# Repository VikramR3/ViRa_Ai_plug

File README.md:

# ViRa AI Plug

A 2-layer ESP32-S3 mains smart plug: an HLK-5M05 isolated module drops 230 V AC to 5 V, an AMS1117 supplies the ESP32-S3-WROOM-1, and an SRD-05VDC relay switches the outlet through a low-side AO3400A MOSFET with a flyback diode and status LED. A DS3231M with a CR1220 backup cell keeps time for scheduled switching, with six buttons and a buzzer for local control and USB-C for programming. Designed in KiCad 10.

## Warning — mains voltage

This board carries 230 V AC. The mains and low-voltage sections are separated by a documented barrier — 6.78 mm of creepage in the open board area, enforced by `ViRa_V1.0.kicad_dru`. However the tightest mains-to-low-voltage gap is **2.10 mm**, at the relay's mains common pad, which is below the 2.5 mm functional minimum and needs the relay or the power module re-placed to fix. It has not been fabricated or tested. Do not connect it to mains.

Circuit topology follows the open-source Zeen-AI-Plug smart plug.

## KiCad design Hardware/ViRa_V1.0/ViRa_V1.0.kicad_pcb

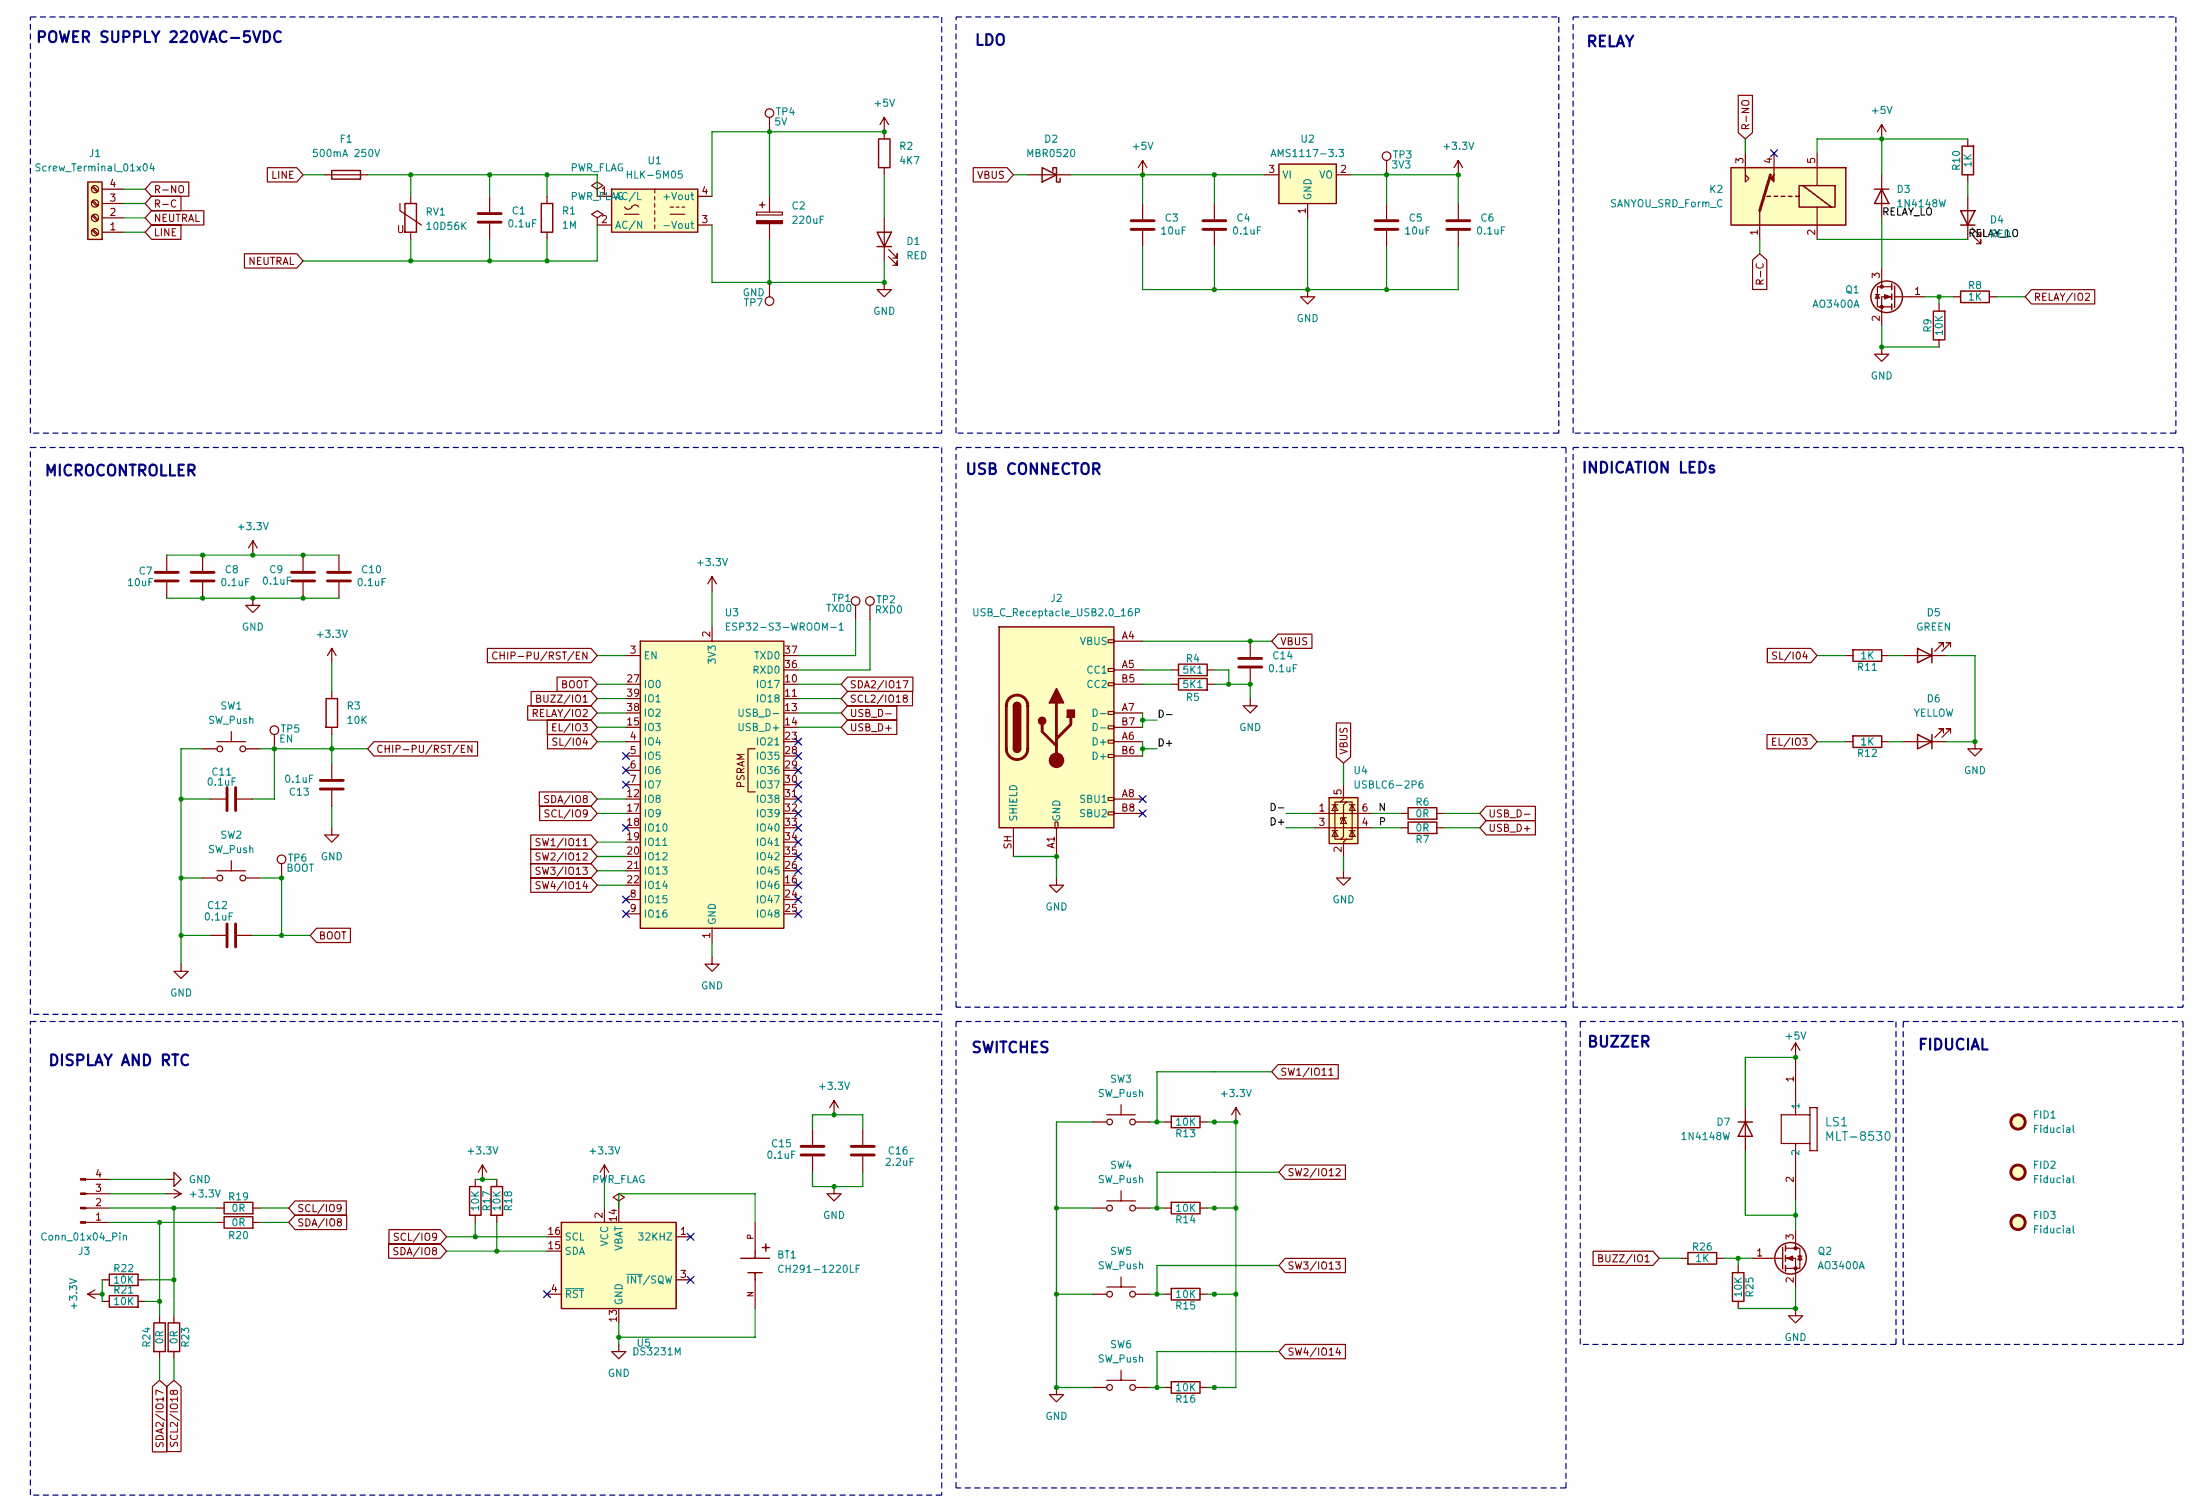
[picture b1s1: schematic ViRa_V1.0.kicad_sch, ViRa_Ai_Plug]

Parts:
BT1: CH291-1220LF; BAT_CH291-1220LF; PARTREV A
C1: 0.1uF; C_Rect_L13.0mm_W6.0mm_P10.00mm_FKS3_FKP3_MKS4
C2: 220uF; CP_Elec_8x10
C3, C5, C7: 10uF; C_0805_2012Metric
C4, C6, C8, C9, C10, C11, C12, C13, C14, C15: 0.1uF; C_0603_1608Metric
C16: 2.2uF; C_0805_2012Metric
D1: RED; LED_D3.0mm
D2: MBR0520; D_SOD-123
D3, D7: 1N4148W; D_SOD-123
D4: RED; LED_0603_1608Metric
D5: GREEN; LED_D3.0mm
D6: YELLOW; LED_D3.0mm
F1: 500mA 250V; Fuse_Littelfuse_395Series
FID1, FID2, FID3: Fiducial; Fiducial_0.75mm_Mask1.5mm
J1: Screw_Terminal_01x04; TerminalBlock_MaiXu_MX126-5.0-04P_1x04_P5.00mm
J2: USB_C_Receptacle_USB2.0_16P; USB_C_Receptacle_HCTL_HC-TYPE-C-16P-01A
J3: Conn_01x04_Pin; PinHeader_1x04_P2.54mm_Vertical
K2: SANYOU_SRD_Form_C; Relay_SPDT_SANYOU_SRD_Series_Form_C
LS1: MLT-8530; MLT-8530_JHE
Q1, Q2: AO3400A; SOT-23
R1: 1M; R_Axial_DIN0207_L6.3mm_D2.5mm_P7.62mm_Horizontal
R2: 4K7; R_0603_1608Metric
R3, R9, R13, R14, R15, R16, R17, R18, R21, R22, R25: 10K; R_0603_1608Metric
R4, R5: 5K1; R_0603_1608Metric
R6, R7, R19, R20, R23, R24: 0R; R_0603_1608Metric
R8, R10, R11, R12, R26: 1K; R_0603_1608Metric
RV1: 10D56K; RV_Disc_D12mm_W5mm_P7.5mm
SW1, SW2, SW3, SW4, SW5, SW6: SW_Push; SW_PUSH_6mm
TP1: TXD0; TestPoint_Pad_D1.5mm
TP2: RXD0; TestPoint_Pad_D1.5mm
TP3: 3V3; TestPoint_Pad_D1.5mm
TP4: 5V; TestPoint_Pad_D1.5mm
TP5: EN; TestPoint_Pad_D1.5mm
TP6: BOOT; TestPoint_Pad_D1.5mm
TP7: GND; TestPoint_Pad_D1.5mm
U1: HLK-5M05; Converter_ACDC_Hi-Link_HLK-5Mxx
U2: AMS1117-3.3; SOT-223-3_TabPin2
U3: ESP32-S3-WROOM-1
U4: USBLC6-2P6; SOT-666
U5: DS3231M; SOIC-16W_7.5x10.3mm_P1.27mm

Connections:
+3.3V: C5.1, C6.1, C7.1, C8.1, C9.1, C10.1, C15.2, C16.1, J3.3, R3.1, R13.1, R14.1, R15.1, R16.1, R17.1, R18.1, R21.1, R22.1, TP3.1 (1_1), U2.2 (VO), U3.2 (3V3), U5.2 (VCC)
+5V: C2.1, C3.1, C4.1, D2.1 (K), D3.1 (K), D7.1 (K), K2.5, LS1.1, R2.1, R10.2, TP4.1 (1_1), U1.4 (+Vout), U2.3 (VI)
/D+: J2.A6 (D+), J2.B6 (D+), U4.3 (I/O2)
/D-: J2.A7 (D-), J2.B7 (D-), U4.1 (I/O1)
/N: R6.1, U4.6 (I/O1)
/P: R7.1, U4.4 (I/O2)
/RELAY_LO: D3.2 (A), D4.1 (K), K2.2, Q1.3 (D)
BOOT: C12.2, SW2.2, TP6.1 (1_1), U3.27 (IO0)
BUZZ/IO1: R26.2, U3.39 (IO1)
CHIP-PU/RST/EN: C11.2, C13.2, R3.2, SW1.2, TP5.1 (1_1), U3.3 (EN)
EL/IO3: R12.2, U3.15 (IO3)
GND: BT1.N, C2.2, C3.2, C4.2, C5.2, C6.2, C7.2, C8.2, C9.2, C10.2, C11.1, C12.1, C13.1, C14.2, C15.1, C16.2, D1.1 (K), D5.1 (K), D6.1 (K), J2.A1 (GND), J2.A12 (GND), J2.B1 (GND), J2.B12 (GND), J2.SH (SHIELD), J3.4, Q1.2 (S), Q2.2 (S), R4.2, R5.2, R9.1, R25.1, SW1.1, SW2.1, SW3.1, SW4.1, SW5.1, SW6.1, TP7.1 (1_1), U1.3 (-Vout), U2.1 (GND), U3.1 (GND), U3.40 (GND), U3.41 (GND), U4.2 (GND), U5.5 (GND), U5.6 (GND), U5.7 (GND), U5.8 (GND), U5.9 (GND), U5.10 (GND), U5.11 (GND), U5.12 (GND), U5.13 (GND)
LINE: F1.1, J1.1
unnamed: D1.2 (A), R2.2
unnamed: D4.2 (A), R10.1
unnamed: D5.2 (A), R11.1
unnamed: D6.2 (A), R12.1
unnamed: D7.2 (A), LS1.2, Q2.3 (D)
unnamed: J2.A5 (CC1), R4.1
unnamed: J2.B5 (CC2), R5.1
unnamed: J3.1, R20.1, R21.2, R24.1
unnamed: J3.2, R19.1, R22.2, R23.1
unnamed: Q1.1 (G), R8.1, R9.2
unnamed: Q2.1 (G), R25.2, R26.1
unnamed: TP2.1 (1_1), U3.36 (RXD0)
unnamed: TP1.1 (1_1), U3.37 (TXD0)
R-C: J1.3, K2.1
R-NO: J1.4, K2.3
RELAY/IO2: R8.2, U3.38 (IO2)
SCL2/IO18: R23.2, U3.11 (IO18)
SCL/IO9: R17.2, R19.2, U3.17 (IO9), U5.16 (SCL)
SDA2/IO17: R24.2, U3.10 (IO17)
SDA/IO8: R18.2, R20.2, U3.12 (IO8), U5.15 (SDA)
SL/I04: R11.2, U3.4 (IO4)
SW1/IO11: R13.2, SW3.2, U3.19 (IO11)
SW2/IO12: R14.2, SW4.2, U3.20 (IO12)
SW3/IO13: R15.2, SW5.2, U3.21 (IO13)
SW4/IO14: R16.2, SW6.2, U3.22 (IO14)
USB_D+: R7.2, U3.14 (USB_D+)
USB_D-: R6.2, U3.13 (USB_D-)
VBUS: C14.1, D2.2 (A), J2.A4 (VBUS), J2.A9 (VBUS), J2.B4 (VBUS), J2.B9 (VBUS), U4.5 (VBUS)

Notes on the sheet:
FIDUCIAL
DISPLAY AND RTC
USB CONNECTOR
LDO
POWER SUPPLY 220VAC-5VDC
INDICATION LEDs
MICROCONTROLLER
BUZZER
RELAY
SWITCHES

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
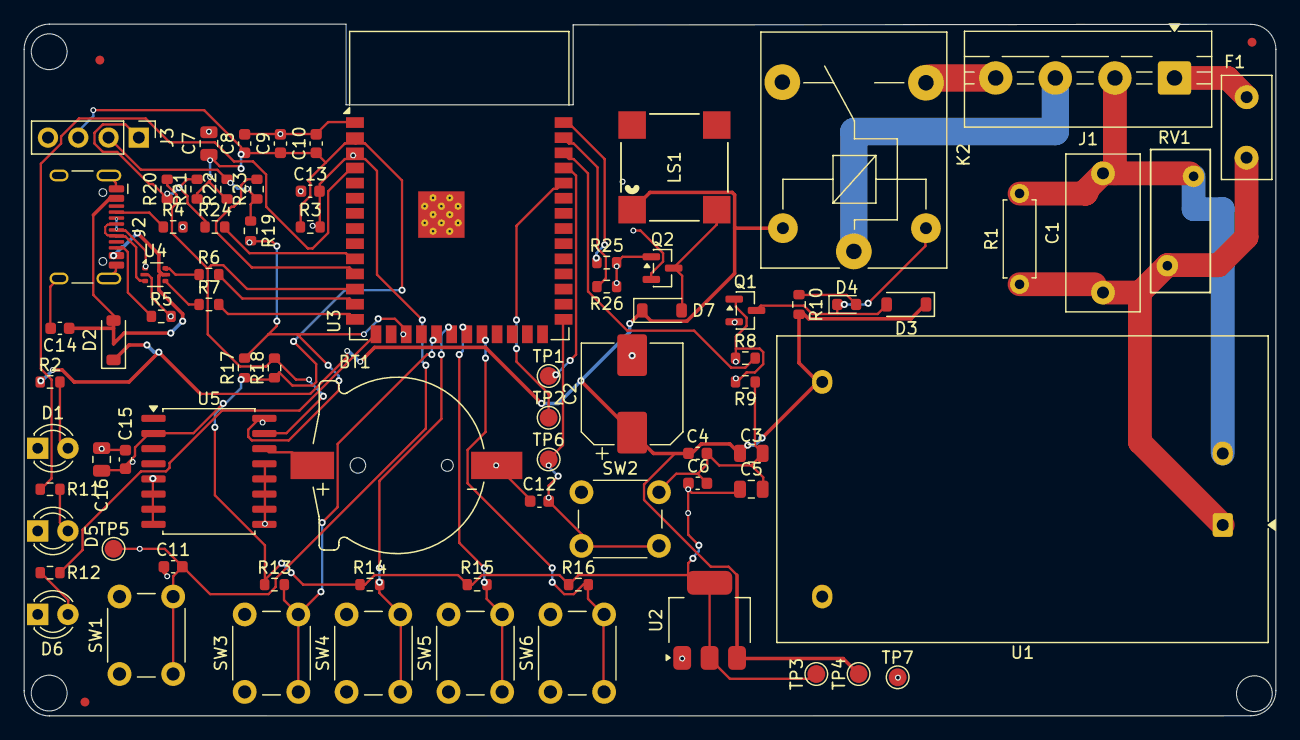
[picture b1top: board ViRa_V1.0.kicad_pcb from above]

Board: 2 copper layers, 105.0 x 58.0 mm, 80 parts (0 on the bottom side), 44 nets.

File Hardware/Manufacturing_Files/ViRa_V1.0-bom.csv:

"Refs","Value","Footprint","Qty","DNP"
"BT1","CH291-1220LF","CH291-1220LF:BAT_CH291-1220LF","1",""
"C1","0.1uF","Capacitor_THT:C_Rect_L13.0mm_W6.0mm_P10.00mm_FKS3_FKP3_MKS4","1",""
"C2","220uF","Capacitor_SMD:CP_Elec_8x10","1",""
"C3","10uF","Capacitor_SMD:C_0805_2012Metric","1",""
"C4","0.1uF","Capacitor_SMD:C_0603_1608Metric","1",""
"C5","10uF","Capacitor_SMD:C_0805_2012Metric","1",""
"C6","0.1uF","Capacitor_SMD:C_0603_1608Metric","1",""
"C7","10uF","Capacitor_SMD:C_0805_2012Metric","1",""
"C8","0.1uF","Capacitor_SMD:C_0603_1608Metric","1",""
"C9","0.1uF","Capacitor_SMD:C_0603_1608Metric","1",""
"C10","0.1uF","Capacitor_SMD:C_0603_1608Metric","1",""
"C11","0.1uF","Capacitor_SMD:C_0603_1608Metric","1",""
"C12","0.1uF","Capacitor_SMD:C_0603_1608Metric","1",""
"C13","0.1uF","Capacitor_SMD:C_0603_1608Metric","1",""
"C14","0.1uF","Capacitor_SMD:C_0603_1608Metric","1",""
"C15","0.1uF","Capacitor_SMD:C_0603_1608Metric","1",""
"C16","2.2uF","Capacitor_SMD:C_0805_2012Metric","1",""
"D1","RED","LED_THT:LED_D3.0mm","1",""
"D2","MBR0520","Diode_SMD:D_SOD-123","1",""
"D3","1N4148W","Diode_SMD:D_SOD-123","1",""
"D4","RED","LED_SMD:LED_0603_1608Metric","1",""
"D5","GREEN","LED_THT:LED_D3.0mm","1",""
"D6","YELLOW","LED_THT:LED_D3.0mm","1",""
"D7","1N4148W","Diode_SMD:D_SOD-123","1",""
"F1","500mA 250V","Fuse:Fuse_Littelfuse_395Series","1",""
"J1","Screw_Terminal_01x04","TerminalBlock:TerminalBlock_MaiXu_MX126-5.0-04P_1x04_P5.00mm","1",""
"J2","USB_C_Receptacle_USB2.0_16P","Connector_USB:USB_C_Receptacle_HCTL_HC-TYPE-C-16P-01A","1",""
"J3","Conn_01x04_Pin","Connector_PinHeader_2.54mm:PinHeader_1x04_P2.54mm_Vertical","1",""
"K2","SANYOU_SRD_Form_C","Relay_THT:Relay_SPDT_SANYOU_SRD_Series_Form_C","1",""
"LS1","MLT-8530","footprints:MLT-8530_JHE","1",""
"Q1","AO3400A","Package_TO_SOT_SMD:SOT-23","1",""
"Q2","AO3400A","Package_TO_SOT_SMD:SOT-23","1",""
"R1","1M","Resistor_THT:R_Axial_DIN0207_L6.3mm_D2.5mm_P7.62mm_Horizontal","1",""
"R2","4K7","Resistor_SMD:R_0603_1608Metric","1",""
"R3","10K","Resistor_SMD:R_0603_1608Metric","1",""
"R4","5K1","Resistor_SMD:R_0603_1608Metric","1",""
"R5","5K1","Resistor_SMD:R_0603_1608Metric","1",""
"R6","0R","Resistor_SMD:R_0603_1608Metric","1",""
"R7","0R","Resistor_SMD:R_0603_1608Metric","1",""
"R8","1K","Resistor_SMD:R_0603_1608Metric","1",""
"R9","10K","Resistor_SMD:R_0603_1608Metric","1",""
"R10","1K","Resistor_SMD:R_0603_1608Metric","1",""
"R11","1K","Resistor_SMD:R_0603_1608Metric","1",""
"R12","1K","Resistor_SMD:R_0603_1608Metric","1",""
"R13","10K","Resistor_SMD:R_0603_1608Metric","1",""
"R14","10K","Resistor_SMD:R_0603_1608Metric","1",""
"R15","10K","Resistor_SMD:R_0603_1608Metric","1",""
"R16","10K","Resistor_SMD:R_0603_1608Metric","1",""
"R17","10K","Resistor_SMD:R_0603_1608Metric","1",""
"R18","10K","Resistor_SMD:R_0603_1608Metric","1",""
"R19","0R","Resistor_SMD:R_0603_1608Metric","1",""
"R20","0R","Resistor_SMD:R_0603_1608Metric","1",""
"R21","10K","Resistor_SMD:R_0603_1608Metric","1",""
"R22","10K","Resistor_SMD:R_0603_1608Metric","1",""
"R23","0R","Resistor_SMD:R_0603_1608Metric","1",""
"R24","0R","Resistor_SMD:R_0603_1608Metric","1",""
"R25","10K","Resistor_SMD:R_0603_1608Metric","1",""
"R26","1K","Resistor_SMD:R_0603_1608Metric","1",""
"RV1","10D56K","Varistor:RV_Disc_D12mm_W5mm_P7.5mm","1",""
"SW1","SW_Push","Button_Switch_THT:SW_PUSH_6mm","1",""
"SW2","SW_Push","Button_Switch_THT:SW_PUSH_6mm","1",""
"SW3","SW_Push","Button_Switch_THT:SW_PUSH_6mm","1",""
"SW4","SW_Push","Button_Switch_THT:SW_PUSH_6mm","1",""
"SW5","SW_Push","Button_Switch_THT:SW_PUSH_6mm","1",""
"SW6","SW_Push","Button_Switch_THT:SW_PUSH_6mm","1",""
"TP1","TXD0","TestPoint:TestPoint_Pad_D1.5mm","1",""
"TP2","RXD0","TestPoint:TestPoint_Pad_D1.5mm","1",""
"TP3","3V3","TestPoint:TestPoint_Pad_D1.5mm","1",""
"TP4","5V","TestPoint:TestPoint_Pad_D1.5mm","1",""
"TP5","EN","TestPoint:TestPoint_Pad_D1.5mm","1",""
"TP6","BOOT","TestPoint:TestPoint_Pad_D1.5mm","1",""
"TP7","GND","TestPoint:TestPoint_Pad_D1.5mm","1",""
"U1","HLK-5M05","Converter_ACDC:Converter_ACDC_Hi-Link_HLK-5Mxx","1",""
"U2","AMS1117-3.3","Package_TO_SOT_SMD:SOT-223-3_TabPin2","1",""
"U3","ESP32-S3-WROOM-1","RF_Module:ESP32-S3-WROOM-1","1",""
"U4","USBLC6-2P6","Package_TO_SOT_SMD:SOT-666","1",""
"U5","DS3231M","Package_SO:SOIC-16W_7.5x10.3mm_P1.27mm","1",""

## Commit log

2025-09-07 ViRa AI Plug: ESP32-S3 mains smart plug with HLK-5M05 supply, SRD-05VDC relay and DS3231M RTC
